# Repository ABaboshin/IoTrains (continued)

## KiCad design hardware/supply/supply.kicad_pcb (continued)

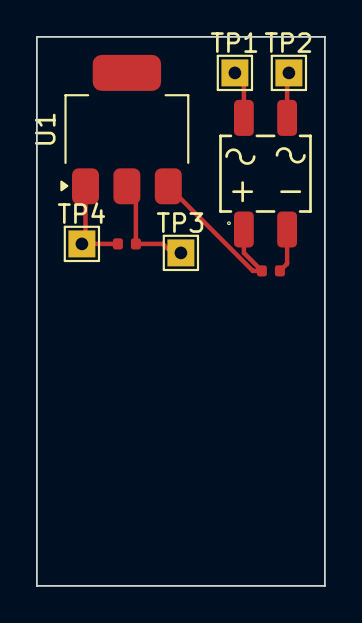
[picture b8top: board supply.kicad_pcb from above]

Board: 2 copper layers, 16.0 x 30.5 mm, 8 parts (0 on the bottom side), 5 nets.

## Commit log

2024-01-29 esp32c3
2024-01-31 wip pio
2024-01-31 basic json schema
2024-01-31 sample cu
2024-01-31 dummy web app
2024-01-31 typescript + generate by json schema
2024-02-01 webpack
2024-02-01 share between frontend and backend
2024-02-01 frontend typescript
2024-02-01 customize schema
2024-02-01 try join
2024-02-01 Revert "try join"
    This reverts commit 8b778f53f09182690da3ec624039e0874b287c5a.
2024-02-02 send from device to backend over mqtt
2024-02-02 send report on timer
2024-02-02 device - backend - frontend
2024-02-02 state
2024-02-02 send status
2024-02-02 expose states to backend
2024-02-02 fix backend
2024-02-02 more fixes
2024-02-04 start mp3
2024-02-04 control unit loop
2024-02-04 rename
2024-02-04 improve schema generation
2024-02-04 download mp3
2024-02-04 documentation
2024-02-04 initial version (#1)
2024-02-07 feat: rfid reader + events queue
2024-02-07 feat: rfid reader + events queue (#2)
2024-02-07 feat: stop play mp3
2024-02-07 feat: stop play mp3 (#3)
2024-02-07 pass command by pointer
2024-02-07 generate from json for hierarchy
2024-02-08 generate to_json for hierarchy
2024-02-08 update typescript
2024-02-08 feat: improve hierarchy parsing (#4)
2024-02-09 fix: play mp3 on esp32
2024-02-09 fix from_json/to_json
2024-02-09 fix: play mp3 on esp32 (#5)
    * fix: play mp3 on esp32
    * fix from_json/to_json
2024-02-09 feat: turnout
2024-02-12 ﻿fix: play mp3 on esp32 (#5)
    * fix: play mp3 on esp32
    * fix from_json/to_json
2024-02-12 feat: turnout (#6)
2024-02-12 json dependency
2024-02-13 gitignore
2024-02-13 refactor: extract library (#7)
2024-02-15 feat: add esp32 wroom, improve mp3
2024-02-15 feat: add esp32 wroom, improve mp3 (#8)
2024-02-18 feat: pwm audio
2024-02-18 feat: pwm audio (#9)
2024-02-18 feat: ldo
2024-02-18 feat: ldo (#10)
2024-02-21 fix: esp32-c3 i2s
2024-02-21 fix: esp32-c3 i2s (#11)
2024-02-22 feat: basic train, documentation
2024-02-22 feat: basic train, documentation (#12)
2024-02-22 feat: introduce capabilities
2024-02-22 feat: introduce capabilities (#13)
2024-02-22 feat: fallback action if no connection
2024-02-22 feat: fallback action if no connection (#14)
2024-02-24 fix: set discriminator
2024-02-24 fix: set discriminator (#15)
2024-02-28 feat: VT95 train
2024-02-28 feat: VT95 train (#16)
2024-02-28 feat: drop down 4 layer
2024-02-28 ams1117
2024-02-28 feat: 4 layers PCB + AMS1117 (#17)
    * feat: drop down 4 layer
    * ams1117
2024-02-29 fix: apply jlcpcb rules
2024-02-29 fix: apply jlcpcb rules (#18)
2024-03-02 feat: MX1508 motor driver
2024-03-02 feat: MX1508 motor driver (#19)
2024-03-05 feat: light
2024-03-05 feat: light (#20)
2024-03-05 feat OTA
2024-03-05 feat OTA (#21)
    * feat OTA
    * gitignore
2024-03-09 feat: multiple rfid, sample train station
2024-03-09 add turnout
2024-03-10 dockerfile
2024-03-10 fix mp3 url player
2024-03-10 fix mp3 player progmem
2024-03-10 push docker
2024-03-10 fix mqtt client buffer
2024-03-11 todo
2024-03-11 feat: multiple rfid, sample train station, fix multiple mp3, docker (#22)
    * feat: multiple rfid, sample train station
    * add turnout
    * dockerfile
    * fix mp3 url player
    * fix mp3 player progmem
    * push docker
2024-03-12 feat: bogie with gears
2024-03-14 bogie with vertical motor
2024-03-14 motor holders
2024-03-14 horizontal bogie
2024-03-14 81-717-714 wall part1
2024-03-14 whole wall test1
2024-03-14 fix to print part1
2024-03-14 fix to print side wall
2024-03-17 part1 with constraints
2024-03-17 side part rebuild
2024-03-17 roof
2024-03-17 seats
2024-03-17 base
2024-03-17 control panel
2024-03-20 tail
2024-03-20 seet6
2024-03-21 hide
2024-03-21 resize roof
2024-03-21 two side parts
2024-03-22 3 sketches
2024-03-22 3 sketches v2
2024-03-22 separator
2024-03-22 seaparator big
2024-03-23 face
2024-03-23 check sizes 1
2024-03-23 714 and 717 full
2024-03-23 vertical bogie recalc
2024-03-23 horizontal bogie recalc
2024-03-25 generate stl
2024-03-25 feat: 81-717/714, bogies (#23)
2024-06-15 81-717/714
2025-05-18 wip power supply
2025-05-19 ldo + motor driver
2025-05-19 gnd zones
2025-05-30 repalce ldo and diode bridge
2025-07-27 add motor driver wip
2025-07-27 feat: rebuild ldo + motordriver (#1)
2025-07-27 feat: cleanup
2025-07-27 feat: cleanup (#2)
2025-07-27 v0.0.0
2025-07-27 pretties
2025-07-27 docker build
2025-07-27 add vite
2025-07-27 tailwind
    todo
    zusstand
    esling config
2025-07-27 cleanup
    TODO
    use zustand
2025-07-27 fix build firmware
2026-02-15 esp32
2026-02-16 TPS629210DRLR
2026-02-22 fix DRC
2026-02-23 wip: - ldo with ams - ldo with TPS629210DRLR - esp32 with usb and connectors - tlc5940
2026-02-24 ams1117 + jst sh
    TODO:
    - jst 1.5mm
    - TPS629210DRLR
    - esp32
    - led driver
2026-02-25 update connectors
2026-02-25 tps6292
2026-02-25 esp32 wip
2026-02-26 regenerate jlcpcb
2026-02-28 simplify usb
2026-02-28 simplify pins and buttons
2026-02-28 esp32 routing
2026-02-28 power supply track sizes
2026-03-01 esp32 rebuild connectors
2026-03-01 some fixes
2026-03-01 tlc5940
2026-03-01 adjustments
2026-03-01 jlcpcb wip
2026-03-04 replace connectors
2026-04-26 tlc5940 code
2026-04-26 fix usb connectors
2026-04-26 esp32 v2
2026-04-29 usbc
2026-04-29 update usb
2026-04-29 cleanup
2026-05-11 wip esp32 v1
2026-05-11 wip esp32 v2
2026-05-18 copy
2026-05-18 Revert "wip esp32 v1"
    This reverts commit 4981c68ebba1a87f50308cda0493b3bcd30c48b4.
2026-05-18 usbc production
2026-06-14 feat: esp32, tlc5940, tps6292/BDR6133, usbc (#3)
2026-06-14 update deps
2026-06-15 adjust pcb max size
